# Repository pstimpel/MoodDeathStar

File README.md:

# MoodDeathStar
A moodlamp and a Death star once had a one night stand...

## Download Death Star stl
https://pinshape.com/items/30200-3d-printed-star-wars-death-star

## 3D Print the stuff
Using my Prusa I3Mk3 I printed the 2 shells in 0.15mm. The inlays were printed in 0.25mm. I was using filament from https://DasFilament.de. I used silver for the shells, and anthracite for the inlays. The housing for the electronics was printed in "nature", and once I ran out of this filament I was using some silver as well. I was printing the Death Star at 150% size. The electronic housing does not need any scaling.

## Buy the stuff you need (all Amazon links are non profit links and just examples for the stuff I bought)
1 switch, has to handle 3A or more https://www.amazon.de/gp/product/B012MCQ2QO

1 Arduino Nano 5V https://www.amazon.de/gp/product/B07H2VT2JN/

1m of RGB LEDs, you need around 40 LEDs https://www.amazon.de/gp/product/B01LSF4QDM

1 power adaptor to 5V DC, 3A https://www.amazon.de/gp/product/B07HSPT57Y

1 matching socket jack https://www.amazon.de/gp/product/B009PH1J5Y

1 USB mini extension 200mm https://www.amazon.de/gp/product/B01MUEAAF0

1 tactile button 6mm https://www.amazon.de/gp/product/B07Q1BXV7T/

2 screw terminals 5mm https://www.amazon.de/gp/product/B07K31L4FH

1 resistor 260 Ohm, 1/4 Watt

1 resistor 10 kOhm, 1/4 Watt

1 Potentiometer 4.7kOhm https://www.amazon.de/gp/product/B07MM4GPWC

3 2.54mm pin connectors https://www.amazon.de/gp/product/B06XR8CV8P

1 tripolar remale 2.54mm connector, like from a servo cable

some cable, has to handle 3A

some cable, doesn't have to handle 3A

a small piece of stripboard to mount the tactile button on it

## Create the PCB, or use a service to do so
Creating the PCB yourself is always fun. I was using toner transfer method, and the sponge method to remove copper from the PCB. If you dislike to work with chemicals, just order the PCB. You can find the layout inside the electronics folder. The layout was created using the famous and almighty KICAD (https://www.kicad.org/).

## Add the electronics to the housing
You need some M3x8mm screws to lock down the pcb, the delock connector, the trigger and the USB. The Tactile button goes a small stripboard piece. Just add two cables around 10cm length each to it, and connect the cables to one of the screw terminals on your main pcb. This while act as a trigger to switch between the different illunmination modes.

## Program your Arduino
Inside the Arduino folder there is an example. Nothing fancy, but maybe a start. The illumination was taken from the many examples they deliver with the FastLED library. I simply added some control for the trigger buttin ad the brightness adjusting potentiometer.

## Create the death star
We work from top to bottom. Add the first five inlayes (1, 2, 3 ,4 ,5) to the top shell - the one without an hole in the middle. In the inlays 6 to 31 add 4 holes using a 10mm drill, kind if a circle shape around the middle hole is our goal. Make sure the holes lines up, so you create kind of 4 channels for the led strips. Now create 4 strips of 10 LED each. Connect 2 strips using 5cm tripolar cable. The + and - cable has to handle 3A. The signal cable does not handle much current. Keep in mind the direction of the data signal. Usually these LED strips work in one direction, only.

    ---> data signal direction --->
    strip 1 --- 3 cable 5cm --- strip 2 --- 3 cable 5cm
    strip 3 --- 3 cable 5cm --- strip 4

Use inlay 6. Add the first pair of connected led strips to holes 1 and 2 - it does not matter if your count holes clockwise or counterclockwise, just stick with your decision. Add second pair of strips to holes 3 and 4. Now add inlay after inlay. After inlay 31 do not forget to add the collar from the death star STLs. Now cut the middle standoff from the botton half of the shell. Cut it so, that you do NOT cut into the mounting point on the bottom. Use some super glue to mount the cut standoff to the collar. Add Inlays 31 to around 10, do not forget to drill 4 holes into each of the inlays, as you did with the first half of the inlays. Once you approach the end of the led strips, use your solder iron again, and connect the the cable of strip 2 to strip 3. 

Drill a hole of 7mm onto the stand, and into the mounting point of the bottom half of your death star. Cut 2 pieces of 40 cm of cable from the 3A capable one, and another piece of 40 cm from your low current cable. Feed the 3 cables from the bottom through the stand, through the mounting hole of the lower death star half into the inner part of the death star. And th left inlays to the bottom half. Use some hot glue to fix them. Now solder the 3 cables to strip 1. Connect the other side of the cable to the servo like connector. 

Run a first test. Working well? Use some super glue to connect both halfs of your death star. Mount the "ball" on top of the stand. Use some super glue to fix it there. Use 2 M3-12mm screws, and mount the top stand to the bottom stand. There are holes you use, just use a longer screw driver and the holes on the bottom of your stand.

Brag with your new illuminated Death star.

Video explaining this project: https://youtu.be/01-m4wZ4NJw

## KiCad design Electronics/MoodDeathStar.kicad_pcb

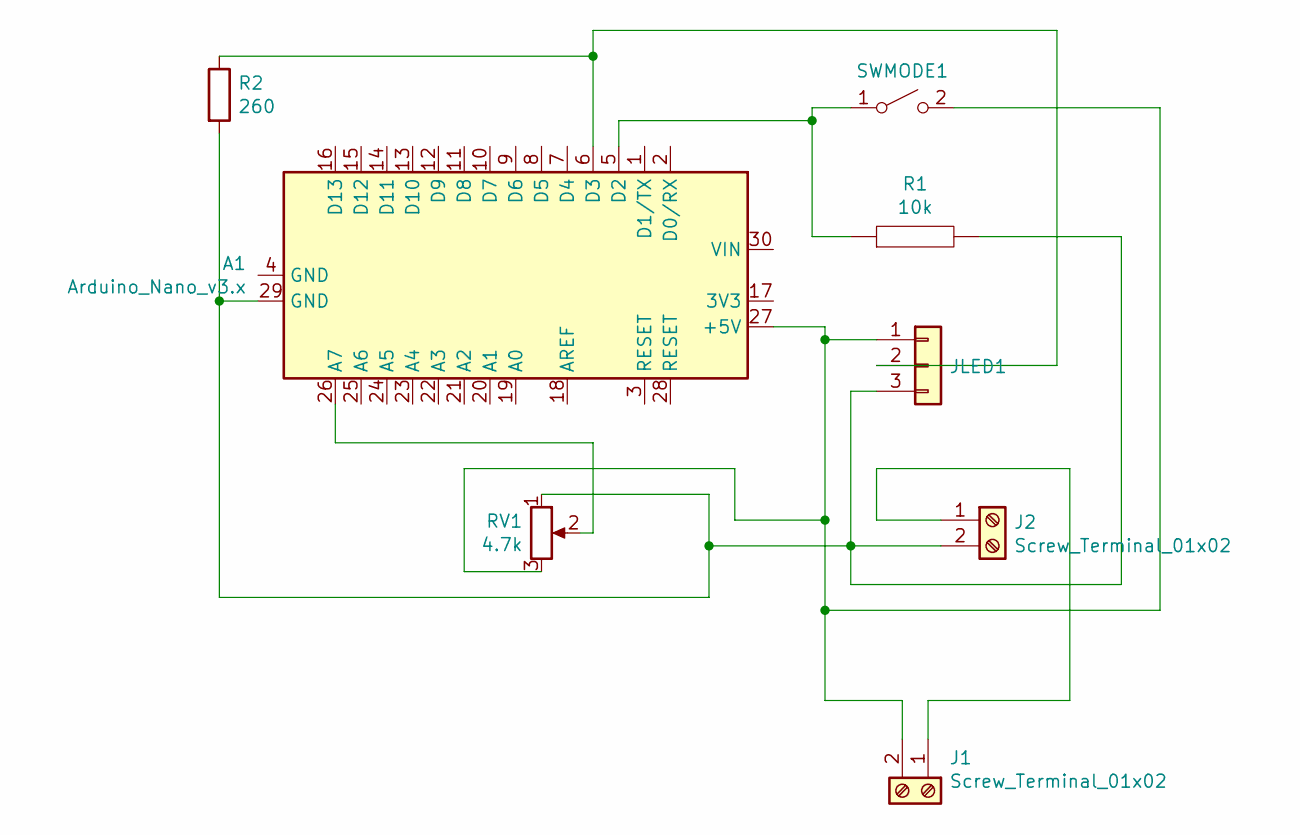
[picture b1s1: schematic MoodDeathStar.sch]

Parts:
A1: Arduino_Nano_v3.x; Arduino_Nano
J1, J2: Screw_Terminal_01x02; TerminalBlock_Altech_AK300-2_P5.00mm
JLED1: Conn_01x03; PinHeader_1x03_P2.54mm_Vertical
R1: 10k; R_Axial_DIN0204_L3.6mm_D1.6mm_P7.62mm_Horizontal
R2: 260; R_Axial_DIN0204_L3.6mm_D1.6mm_P7.62mm_Horizontal
RV1: 4.7k; Potentiometer_Alps_RK163_Single_Horizontal
SWMODE1: s; PinHeader_1x02_P2.54mm_Vertical

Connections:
unnamed: A1.5 (D2), R1.1, SWMODE1.1 (A)
unnamed: A1.6 (D3), JLED1.2, R2.1
unnamed: A1.26 (A7), RV1.2
unnamed: A1.27 (+5V), J1.2, JLED1.1, RV1.3, SWMODE1.2 (B)
unnamed: A1.29 (GND), J2.2, JLED1.3, R1.2, R2.2, RV1.1
unnamed: J1.1, J2.1

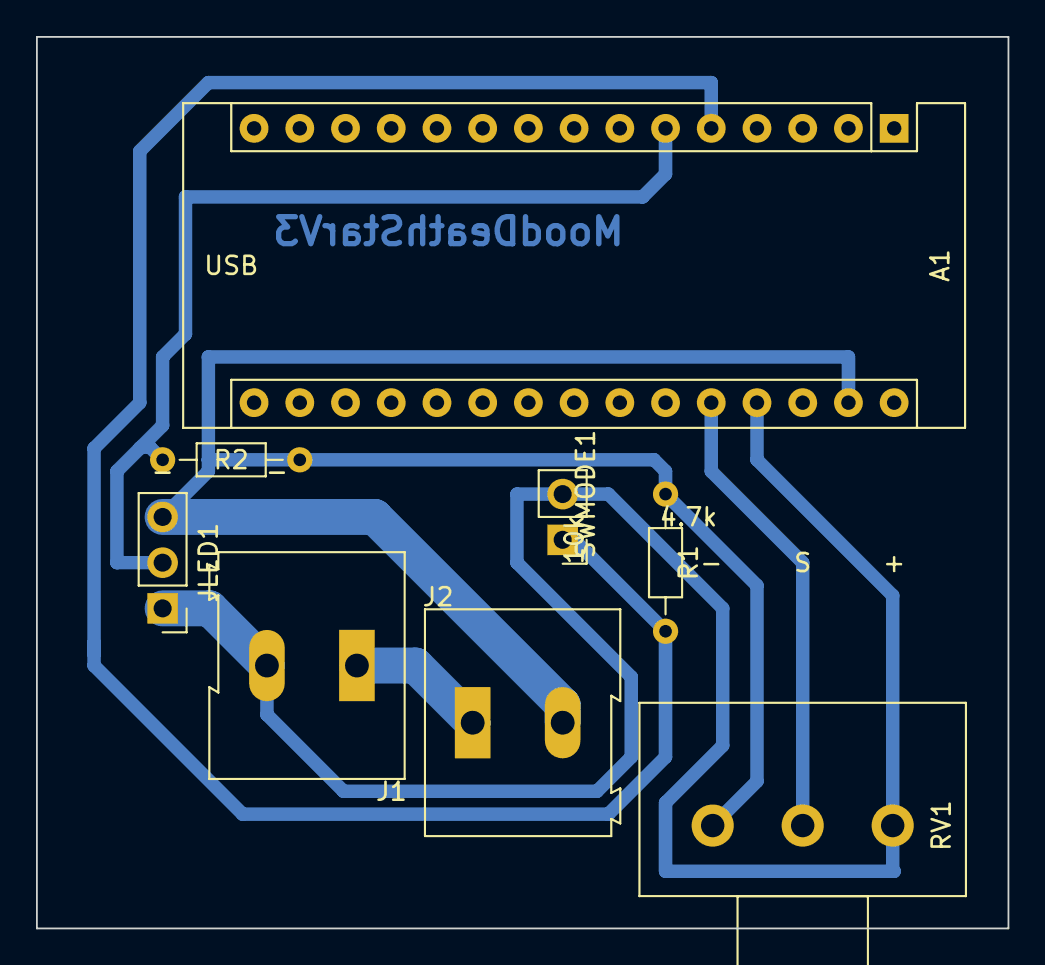
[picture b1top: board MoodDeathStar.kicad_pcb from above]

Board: 2 copper layers, 54.0 x 49.5 mm, 8 parts (0 on the bottom side), 6 nets.

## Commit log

2019-09-15 Initial Added STL files Added circuit layout and pcb
2019-09-15 Readme
2019-09-15 Finalize readme and add Arduino stuff
2019-09-15 Some more illumination modes
2021-11-08 Update README.md
    https://forum.kicad.info/t/warning-avoid-all-links-to-kicad-pcb-org-use-kicad-org/31521
